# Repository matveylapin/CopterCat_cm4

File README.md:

# CopterCat_cm4

Полётный контроллер для стандарта FMU-v6u. Обычно на дронах для программирования устанавливают полётный контроллер, одноплатный компьютер и иногда arduino. Почему бы не объединить это в одну плату (ну или компактный стек), это уменьшит габариты и вес. В качестве arduino мы выбрали чип ESP32, это позволит организовывать из нескольких подобных плат одну независимую сеть для коммуникации между дронами.

## Спецификация 

### FMU
* STM32H753IIK6 480Mhz Cortex-M7
* 2Mb + 256Kb FLASH
* 1Mb RAM
* ICM20602, ICM42605, BMI088, BMP388, BMM150
* Полностью совместима со стандартом FMU-v6u
### Raspberry Pi
* Поддержка платы RPi CM4 
* Слот для SD-карты
* Возможность прошивки встроенной eMMC
* CAT24C256 EEPROM
* Поддержка 2 камер(CAM0-две линия, CAM1-четыре линии)
* Поддержка USB-OTG
### ESP32
* 16MB внешней FLASH (W25Q128JVS)
* 8MB внешней PSRAM (LY68L6400SLIT)
* Встроенная антенна
* USB-TTL конвертор
### Остальное
* USB-HUB USB2514B
* USB-PD с физическим переключением
* Связь ESP32 и STM32 через UART
* 3 варианта питания
* 4 универсальных GPIO от ESP32
* USB Type-C
* Размеры 40x55 мм, плата 4 слоя
___

## Разьёмы и перемычки

1. GPIO ESP32 4 порта ввода вывода для подключения внешнего оборудования
2. Коннекторы RPi CM4
3. Выводы ESC 8 шт
4. Контакты программирования и отладки JTAG STM32
5. Коннекторы камер (шлейф 22 контакта с 0.5 мм расстояния между проводниками)
6. Контакт подключения адресной ленты
7. Контакты основного питания 5В
8. JST-6 стандартного шлейфа питания PX4 
9. JST-6 GPS+компас+5В
10. JST-4 I2C+5В
11. USB Type-C
12. JST-4 UART7+5В
13. JST-4 I2C RPi+3.3B для подключения дальномера
14. JST-4 UART5+5В
15. JST-5 Стандартный разъём для подключения приёмника управления
16. Слот SD карты (для RPi)
17. Джампер BOOT для STM32
18. Джампер RPIBOOT для прошивки eMMC модуля RPi CM4
19. Джампер переключения режима работы USB разъёма (при замкнутой перемычке, USB работает как вход HUB и при подключении к компьютеру будут отборажаться STM32, ESP32 и RPi CM4 в режиме OTG; при разомкнутой перемычке, USB будет работать для подключения внешних устройств к RPi, например стерео-камеры)
___

## Загрузка прошивки
### FMU
При первом запуске, в микроконтреллер придётся загрузить PX4-bootloader через порт JTAG. Подробная инструкция [здесь](https://docs.px4.io/master/en/software_update/stm32_bootloader.html#stm32-bootloader).

Для подключения к компьютеру:
1. Замкните перемычку 19
2. Подключите USB Type-C к компьютеру
3. Устройство должно появиться в [QGC](http://qgroundcontrol.com)

Также прошивку можно произвести через RPi:
1. Установите RPi CM4 в коннектор на плате
2. Разомкните перемычку 19
3. Устройство появиться в папке /dev на RPi

### ESP32
Написать программу можно либо в [Arduino IDE](https://www.arduino.cc/en/software), либо в [VS Code](https://code.visualstudio.com) с плагином [esp-idf](https://habr.com/ru/post/530638/). Далее скомпилировать и загрузить в микроконтроллер. Загрузить можно двумя способами.

С компьютера:
1. Замкните перемычку 19
2. В подключённых устройствах появиться CP2104
3. Загрузите прошивку в соотвествии с инструкцией к выбранной IDE

С RPi CM4:
1. Установите RPi CM4 в коннектор на плате
2. Разомкните перемычку 19
3. Скомпилируйте ваш код в .bin формат
4. Загрузите полученный файл на RPi
5. Загрузите прошивку в микроконтроллер с помощью esptool.py ([описание+установка](https://docs.espressif.com/projects/esptool/en/latest/esp32/index.html))

Так же ESP32 подключен к STM32 по UART, это позволит связывть между собой не просто RPi, а сразу FMU.

### RPi CM4
Слот SD карты работает как на стандартной RPi. Для плат с eMMC порядок загрузки операционной системы не отличается от CM4 IO Board ([инструкция](https://www.jeffgeerling.com/blog/2020/how-flash-raspberry-pi-os-compute-module-4-emmc-usbboot)).

___

## Общая информация
* Все требуемые для заказа файлы находится в папке /gerbers.
* Проект выполнен в программе [KiCAD v6](https://www.kicad.org)
* Библиотеки компонентов взяты с сайта [snapeda](https://www.snapeda.com)

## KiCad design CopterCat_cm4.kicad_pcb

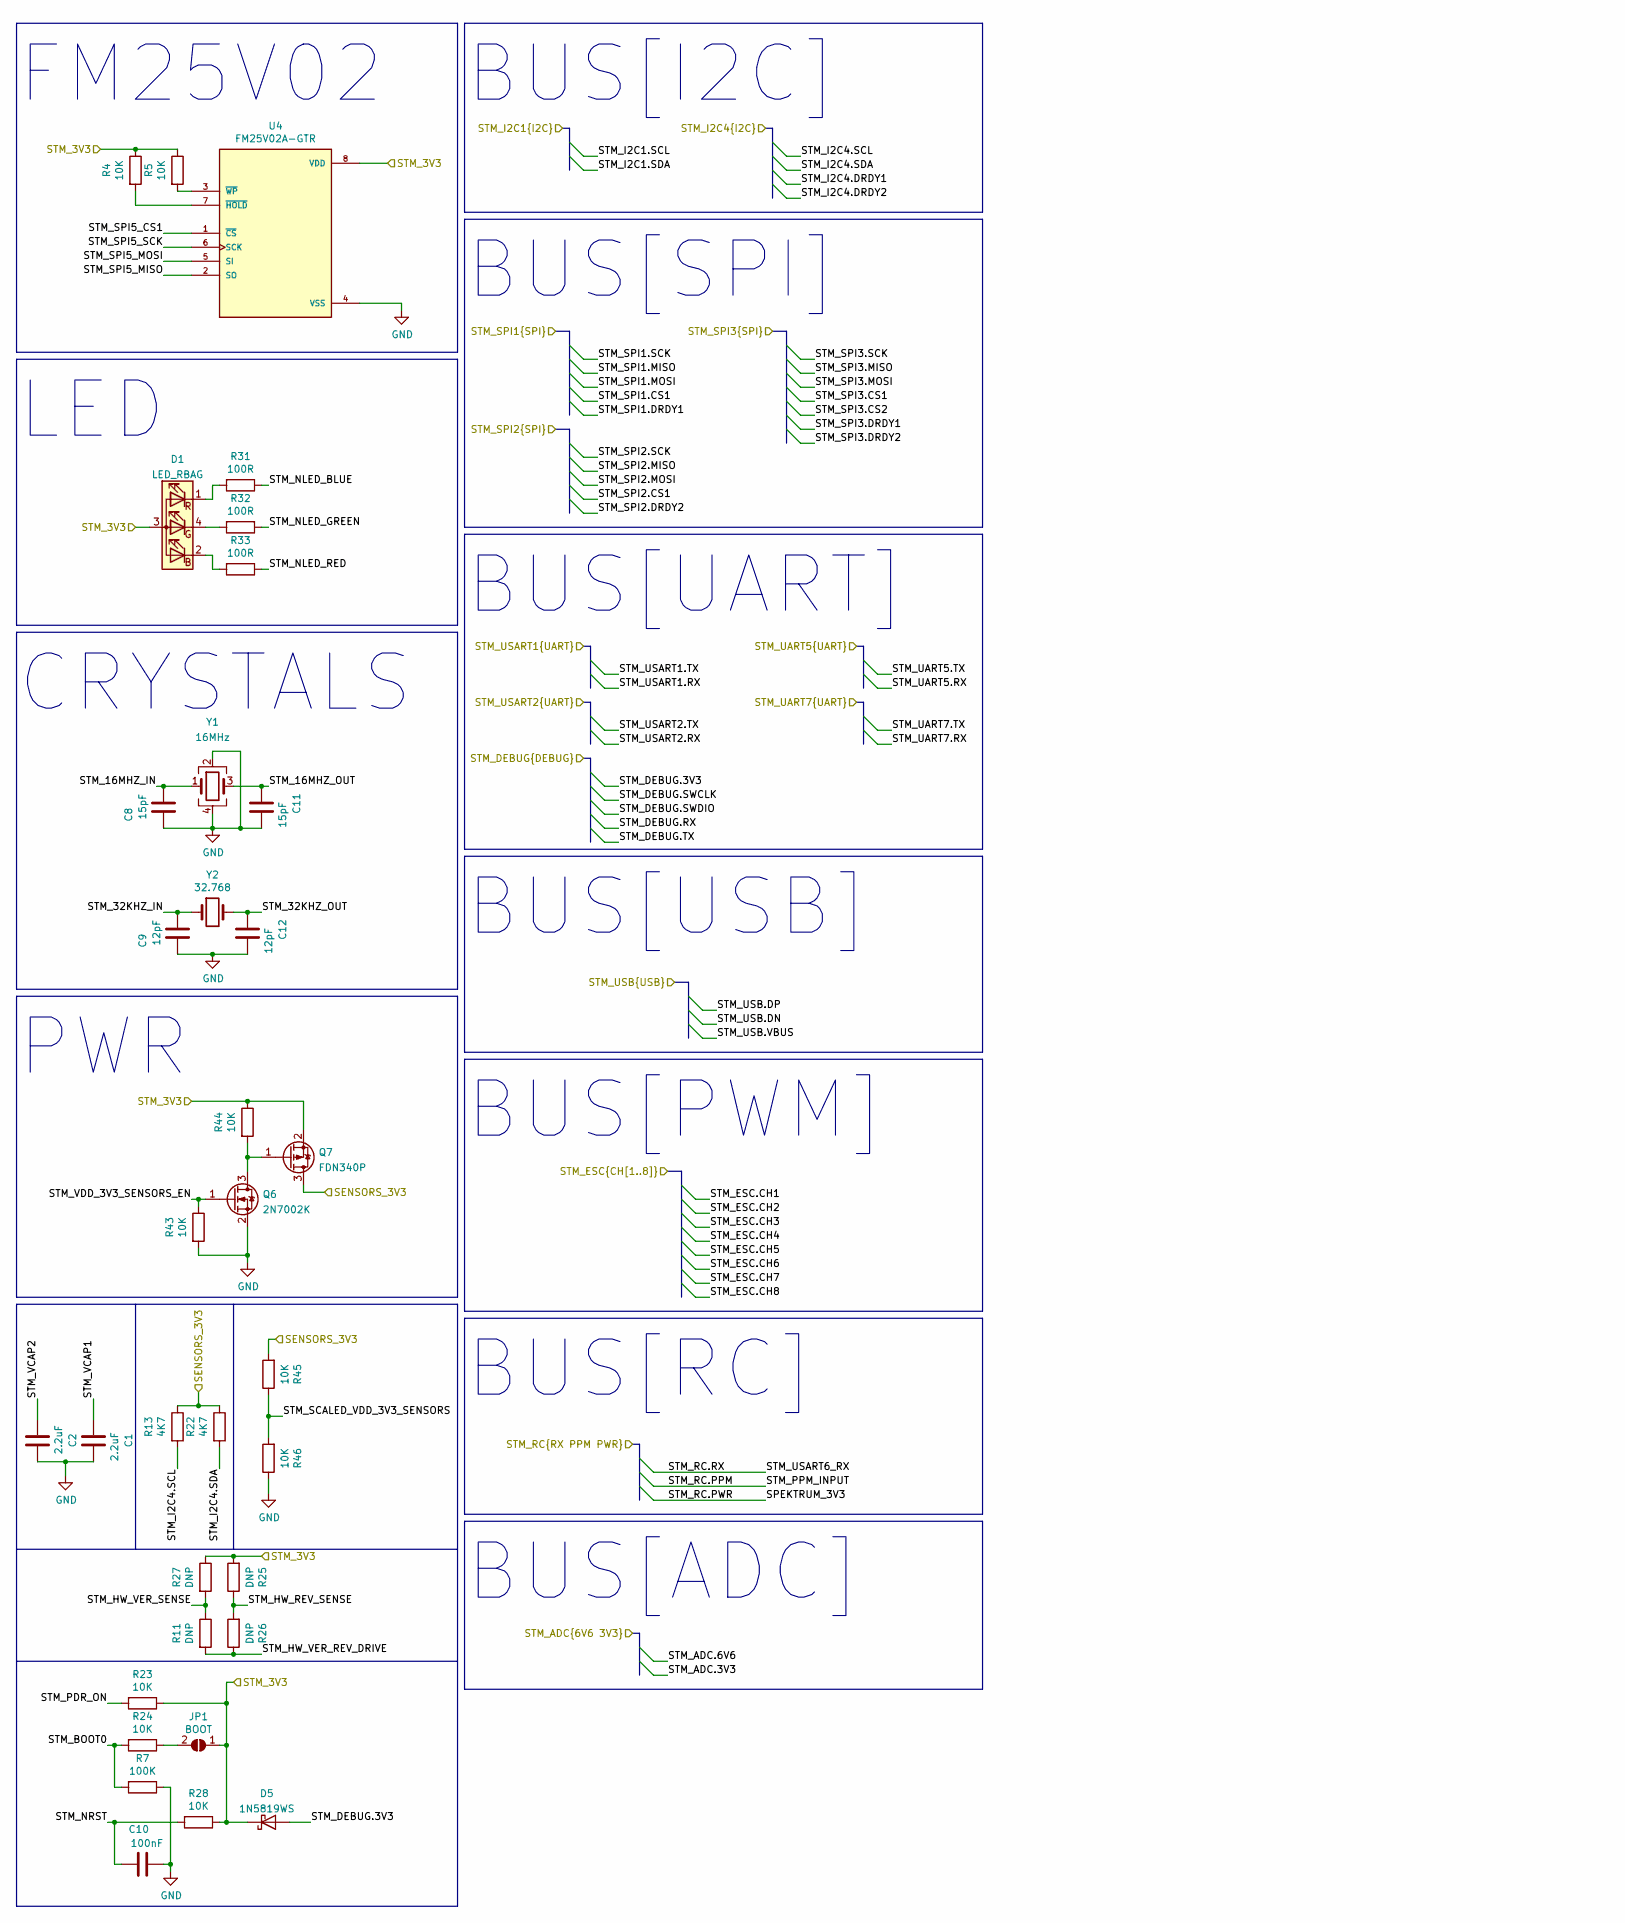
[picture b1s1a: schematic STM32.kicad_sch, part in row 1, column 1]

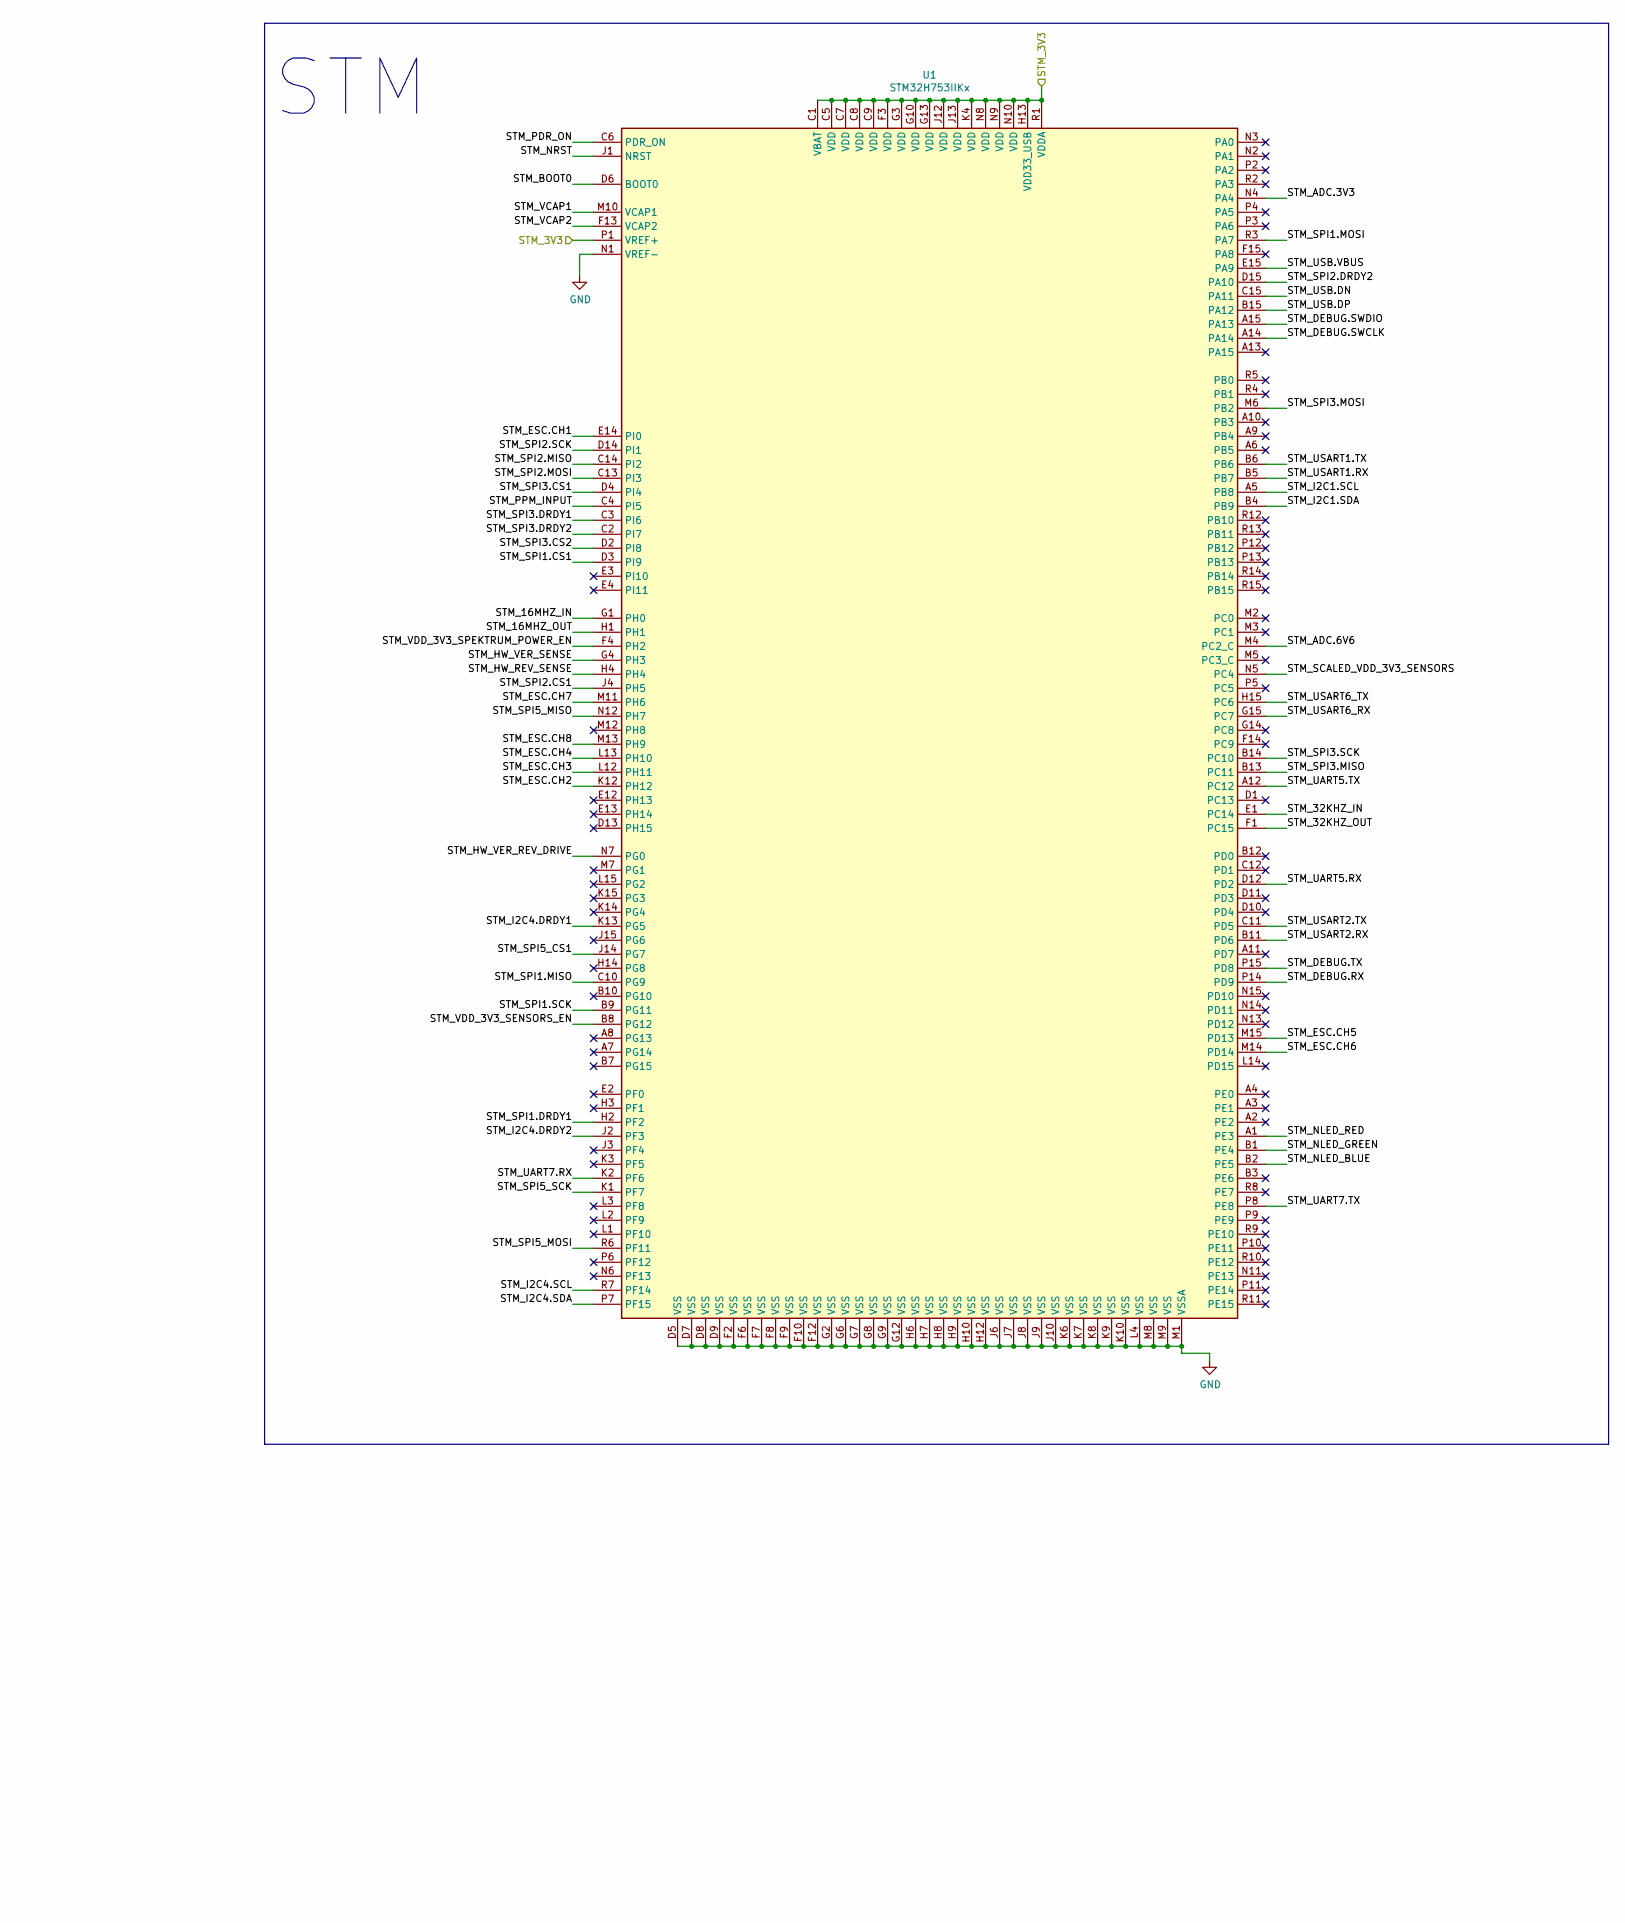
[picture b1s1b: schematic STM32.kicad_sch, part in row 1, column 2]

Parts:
C1, C2: 2.2uF; C_0402_1005Metric
C8, C11: 15pF; C_0402_1005Metric
C9, C12: 12pF; C_0402_1005Metric
C10: 100nF; C_0402_1005Metric
D1: LED_RBAG; LED_Cree-PLCC4_2x2mm_CW; Manufacturer_Part_Number FM-B2020RGBA-HG
D5: 1N5819WS; D_SOD-323; Manufacturer_Part_Number 1N5819WS
JP1: BOOT; SolderJumper-2_P1.3mm_Open_RoundedPad1.0x1.5mm
Q6: 2N7002K; SOT-23; Manufacturer_Part_Number 2N7002,215
Q7: FDN340P; SOT-23; Manufacturer_Part_Number FDN340P
R4, R5, R23, R24, R28, R43, R44, R45, R46: 10K; R_0402_1005Metric
R7: 100K; R_0402_1005Metric
R11, R25, R26, R27: DNP; R_0402_1005Metric
R13, R22: 4K7; R_0402_1005Metric
R31, R32, R33: 100R; R_0402_1005Metric
U1: STM32H753IIKx; UFBGA-201_10x10mm_Layout15x15_P0.65mm; Manufacturer_Part_Number STM32H753IIK6
U4: FM25V02A-GTR; SOIC127P602X172-8N; Manufacturer_Part_Number FM25V02A-GTR
Y1: 16MHz; Crystal_SMD_2016-4Pin_2.0x1.6mm; Manufacturer_Part_Number OT201616MJBA4SL
Y2: 32.768; Crystal_SMD_MicroCrystal_CM9V-T1A-2Pin_1.6x1.0mm; Manufacturer_Part_Number SC-16S

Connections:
/Connectors/STM_ADC.3V3: U1.N4 (PA4); also elsewhere on the board
/Connectors/STM_ADC.6V6: U1.M4 (PC2_C); also elsewhere on the board
/Connectors/STM_DEBUG.3V3: D5.2 (A); also elsewhere on the board
/Connectors/STM_DEBUG.RX: U1.P14 (PD9); also elsewhere on the board
/Connectors/STM_DEBUG.SWCLK: U1.A14; also elsewhere on the board
/Connectors/STM_DEBUG.SWDIO: U1.A15 (PA13); also elsewhere on the board
/Connectors/STM_DEBUG.TX: U1.P15 (PD8); also elsewhere on the board
/Connectors/STM_ESC.CH1: U1.E14 (PI0); also elsewhere on the board
/Connectors/STM_ESC.CH2: U1.K12 (PH12); also elsewhere on the board
/Connectors/STM_ESC.CH3: U1.L12 (PH11); also elsewhere on the board
/Connectors/STM_ESC.CH4: U1.L13 (PH10); also elsewhere on the board
/Connectors/STM_ESC.CH5: U1.M15 (PD13); also elsewhere on the board
/Connectors/STM_ESC.CH6: U1.M14 (PD14); also elsewhere on the board
/Connectors/STM_ESC.CH7: U1.M11 (PH6); also elsewhere on the board
/Connectors/STM_ESC.CH8: U1.M13 (PH9); also elsewhere on the board
/Connectors/STM_I2C1.SCL: U1.A5 (PB8); also elsewhere on the board
/Connectors/STM_I2C1.SDA: U1.B4 (PB9); also elsewhere on the board
/Connectors/STM_RC.PPM: U1.C4 (PI5); also elsewhere on the board
/Connectors/STM_RC.RX: U1.G15 (PC7); also elsewhere on the board
/Connectors/STM_UART5.RX: U1.D12 (PD2); also elsewhere on the board
/Connectors/STM_UART5.TX: U1.A12 (PC12); also elsewhere on the board
/Connectors/STM_UART7.RX: U1.K2 (PF6); also elsewhere on the board
/Connectors/STM_UART7.TX: U1.P8 (PE8); also elsewhere on the board
/Connectors/STM_USART1.RX: U1.B5 (PB7); also elsewhere on the board
/Connectors/STM_USART1.TX: U1.B6; also elsewhere on the board
/ESP32/ESP_UART1.RX: U1.B11 (PD6); also elsewhere on the board
/ESP32/ESP_UART1.TX: U1.C11 (PD5); also elsewhere on the board
/Power/3V3_GROUP1: D1.3 (A), D5.1 (K), JP1.1 (A), Q7.2 (S), R4.1, R5.1, R23.1, R25.2, R27.1, R28.1, R44.1, U1.C1 (VBAT), U1.C5 (VDD), U1.C7 (VDD), U1.C8 (VDD), U1.C9 (VDD), U1.F3 (VDD), U1.G3 (VDD), U1.G10 (VDD), U1.G13 (VDD), U1.H13 (VDD33_USB), U1.J12 (VDD), U1.J13 (VDD), U1.K4 (VDD), U1.N8 (VDD), U1.N9 (VDD), U1.N10 (VDD), U1.P1 (VREF+), U1.R1 (VDDA), U4.8 (VDD); also elsewhere on the board
/STM32/SENSORS_3V3: Q7.3 (D), R13.1, R22.1, R45.2; also elsewhere on the board
/STM32/STM_16MHZ_IN: C8.2, U1.G1 (PH0), Y1.1
/STM32/STM_16MHZ_OUT: C11.1, U1.H1, Y1.3
/STM32/STM_32KHZ_IN: C9.2, U1.E1 (PC14), Y2.1
/STM32/STM_32KHZ_OUT: C12.1, U1.F1 (PC15), Y2.2
/STM32/STM_BOOT0: R7.2, R24.2, U1.D6 (BOOT0)
/STM32/STM_HW_REV_SENSE: R25.1, R26.2, U1.H4
/STM32/STM_HW_VER_REV_DRIVE: R11.2, R26.1, U1.N7 (PG0)
/STM32/STM_HW_VER_SENSE: R11.1, R27.2, U1.G4 (PH3)
/STM32/STM_I2C4.DRDY1: U1.K13 (PG5); also elsewhere on the board
/STM32/STM_I2C4.DRDY2: U1.J2 (PF3); also elsewhere on the board
/STM32/STM_I2C4.SCL: R13.2, U1.R7 (PF14); also elsewhere on the board
/STM32/STM_I2C4.SDA: R22.2, U1.P7 (PF15); also elsewhere on the board
/STM32/STM_NLED_BLUE: R31.1, U1.B2 (PE5)
/STM32/STM_NLED_GREEN: R32.2, U1.B1 (PE4)
/STM32/STM_NLED_RED: R33.1, U1.A1 (PE3)
/STM32/STM_NRST: C10.1, R28.2, U1.J1 (NRST)
/STM32/STM_PDR_ON: R23.2, U1.C6 (PDR_ON)
/STM32/STM_SCALED_VDD_3V3_SENSORS: R45.1, R46.2, U1.N5 (PC4)
/STM32/STM_SPI1.CS1: U1.D3 (PI9); also elsewhere on the board
/STM32/STM_SPI1.DRDY1: U1.H2 (PF2); also elsewhere on the board
/STM32/STM_SPI1.MISO: U1.C10 (PG9); also elsewhere on the board
/STM32/STM_SPI1.MOSI: U1.R3 (PA7); also elsewhere on the board
/STM32/STM_SPI1.SCK: U1.B9 (PG11); also elsewhere on the board
/STM32/STM_SPI2.CS1: U1.J4 (PH5); also elsewhere on the board
/STM32/STM_SPI2.DRDY2: U1.D15 (PA10); also elsewhere on the board
/STM32/STM_SPI2.MISO: U1.C14 (PI2); also elsewhere on the board
/STM32/STM_SPI2.MOSI: U1.C13 (PI3); also elsewhere on the board
/STM32/STM_SPI2.SCK: U1.D14 (PI1); also elsewhere on the board
/STM32/STM_SPI3.CS1: U1.D4 (PI4); also elsewhere on the board
/STM32/STM_SPI3.CS2: U1.D2 (PI8); also elsewhere on the board
/STM32/STM_SPI3.DRDY1: U1.C3 (PI6); also elsewhere on the board
/STM32/STM_SPI3.DRDY2: U1.C2 (PI7); also elsewhere on the board
/STM32/STM_SPI3.MISO: U1.B13 (PC11); also elsewhere on the board
/STM32/STM_SPI3.MOSI: U1.M6 (PB2); also elsewhere on the board
/STM32/STM_SPI3.SCK: U1.B14 (PC10); also elsewhere on the board
/STM32/STM_SPI5_CS1: U1.J14 (PG7), U4.1 (~CS)
/STM32/STM_SPI5_MISO: U1.N12 (PH7), U4.2 (SO)
/STM32/STM_SPI5_MOSI: U1.R6 (PF11), U4.5 (SI)
/STM32/STM_SPI5_SCK: U1.K1 (PF7), U4.6 (SCK)
/STM32/STM_USART6_TX: U1.H15 (PC6)
/STM32/STM_USB.DN: U1.C15 (PA11); also elsewhere on the board
/STM32/STM_USB.DP: U1.B15 (PA12); also elsewhere on the board
/STM32/STM_USB.VBUS: U1.E15 (PA9); also elsewhere on the board
/STM32/STM_VCAP1: C1.1, U1.M10 (VCAP1)
/STM32/STM_VCAP2: C2.1, U1.F13 (VCAP2)
/STM32/STM_VDD_3V3_SENSORS_EN: Q6.1 (G), R43.1, U1.B8 (PG12)
/STM32/STM_VDD_3V3_SPEKTRUM_POWER_EN: U1.F4 (PH2)
GND: C1.2, C2.2, C8.1, C9.1, C10.2, C11.2, C12.2, Q6.2 (S), R7.1, R43.2, R46.1, U1.D5 (VSS), U1.D7 (VSS), U1.D8 (VSS), U1.D9 (VSS), U1.F2 (VSS), U1.F6 (VSS), U1.F7 (VSS), U1.F8 (VSS), U1.F9 (VSS), U1.F10 (VSS), U1.F12 (VSS), U1.G2 (VSS), U1.G6 (VSS), U1.G7 (VSS), U1.G8 (VSS), U1.G9 (VSS), U1.G12 (VSS), U1.H6 (VSS), U1.H7 (VSS), U1.H8 (VSS), U1.H9 (VSS), U1.H10 (VSS), U1.H12 (VSS), U1.J6 (VSS), U1.J7 (VSS), U1.J8 (VSS), U1.J9 (VSS), U1.J10 (VSS), U1.K6 (VSS), U1.K7 (VSS), U1.K8 (VSS), U1.K9 (VSS), U1.K10 (VSS), U1.L4 (VSS), U1.M1 (VSSA), U1.M8 (VSS), U1.M9 (VSS), U1.N1 (VREF-), U4.4 (VSS), Y1.2, Y1.4; also elsewhere on the board
unnamed: D1.1 (RK), R31.2
unnamed: D1.2 (BK), R33.2
unnamed: D1.4 (GK), R32.1
unnamed: JP1.2 (B), R24.1
unnamed: Q6.3 (D), Q7.1 (G), R44.2
unnamed: R4.2, U4.7 (~HOLD)
unnamed: R5.2, U4.3 (~WP)

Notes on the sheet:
BUS[RC]
BUS[SPI]
PWR
BUS[UART]
CRYSTALS
FM25V02
BUS[USB]
STM
BUS[ADC]
LED
BUS[PWM]
BUS[I2C]

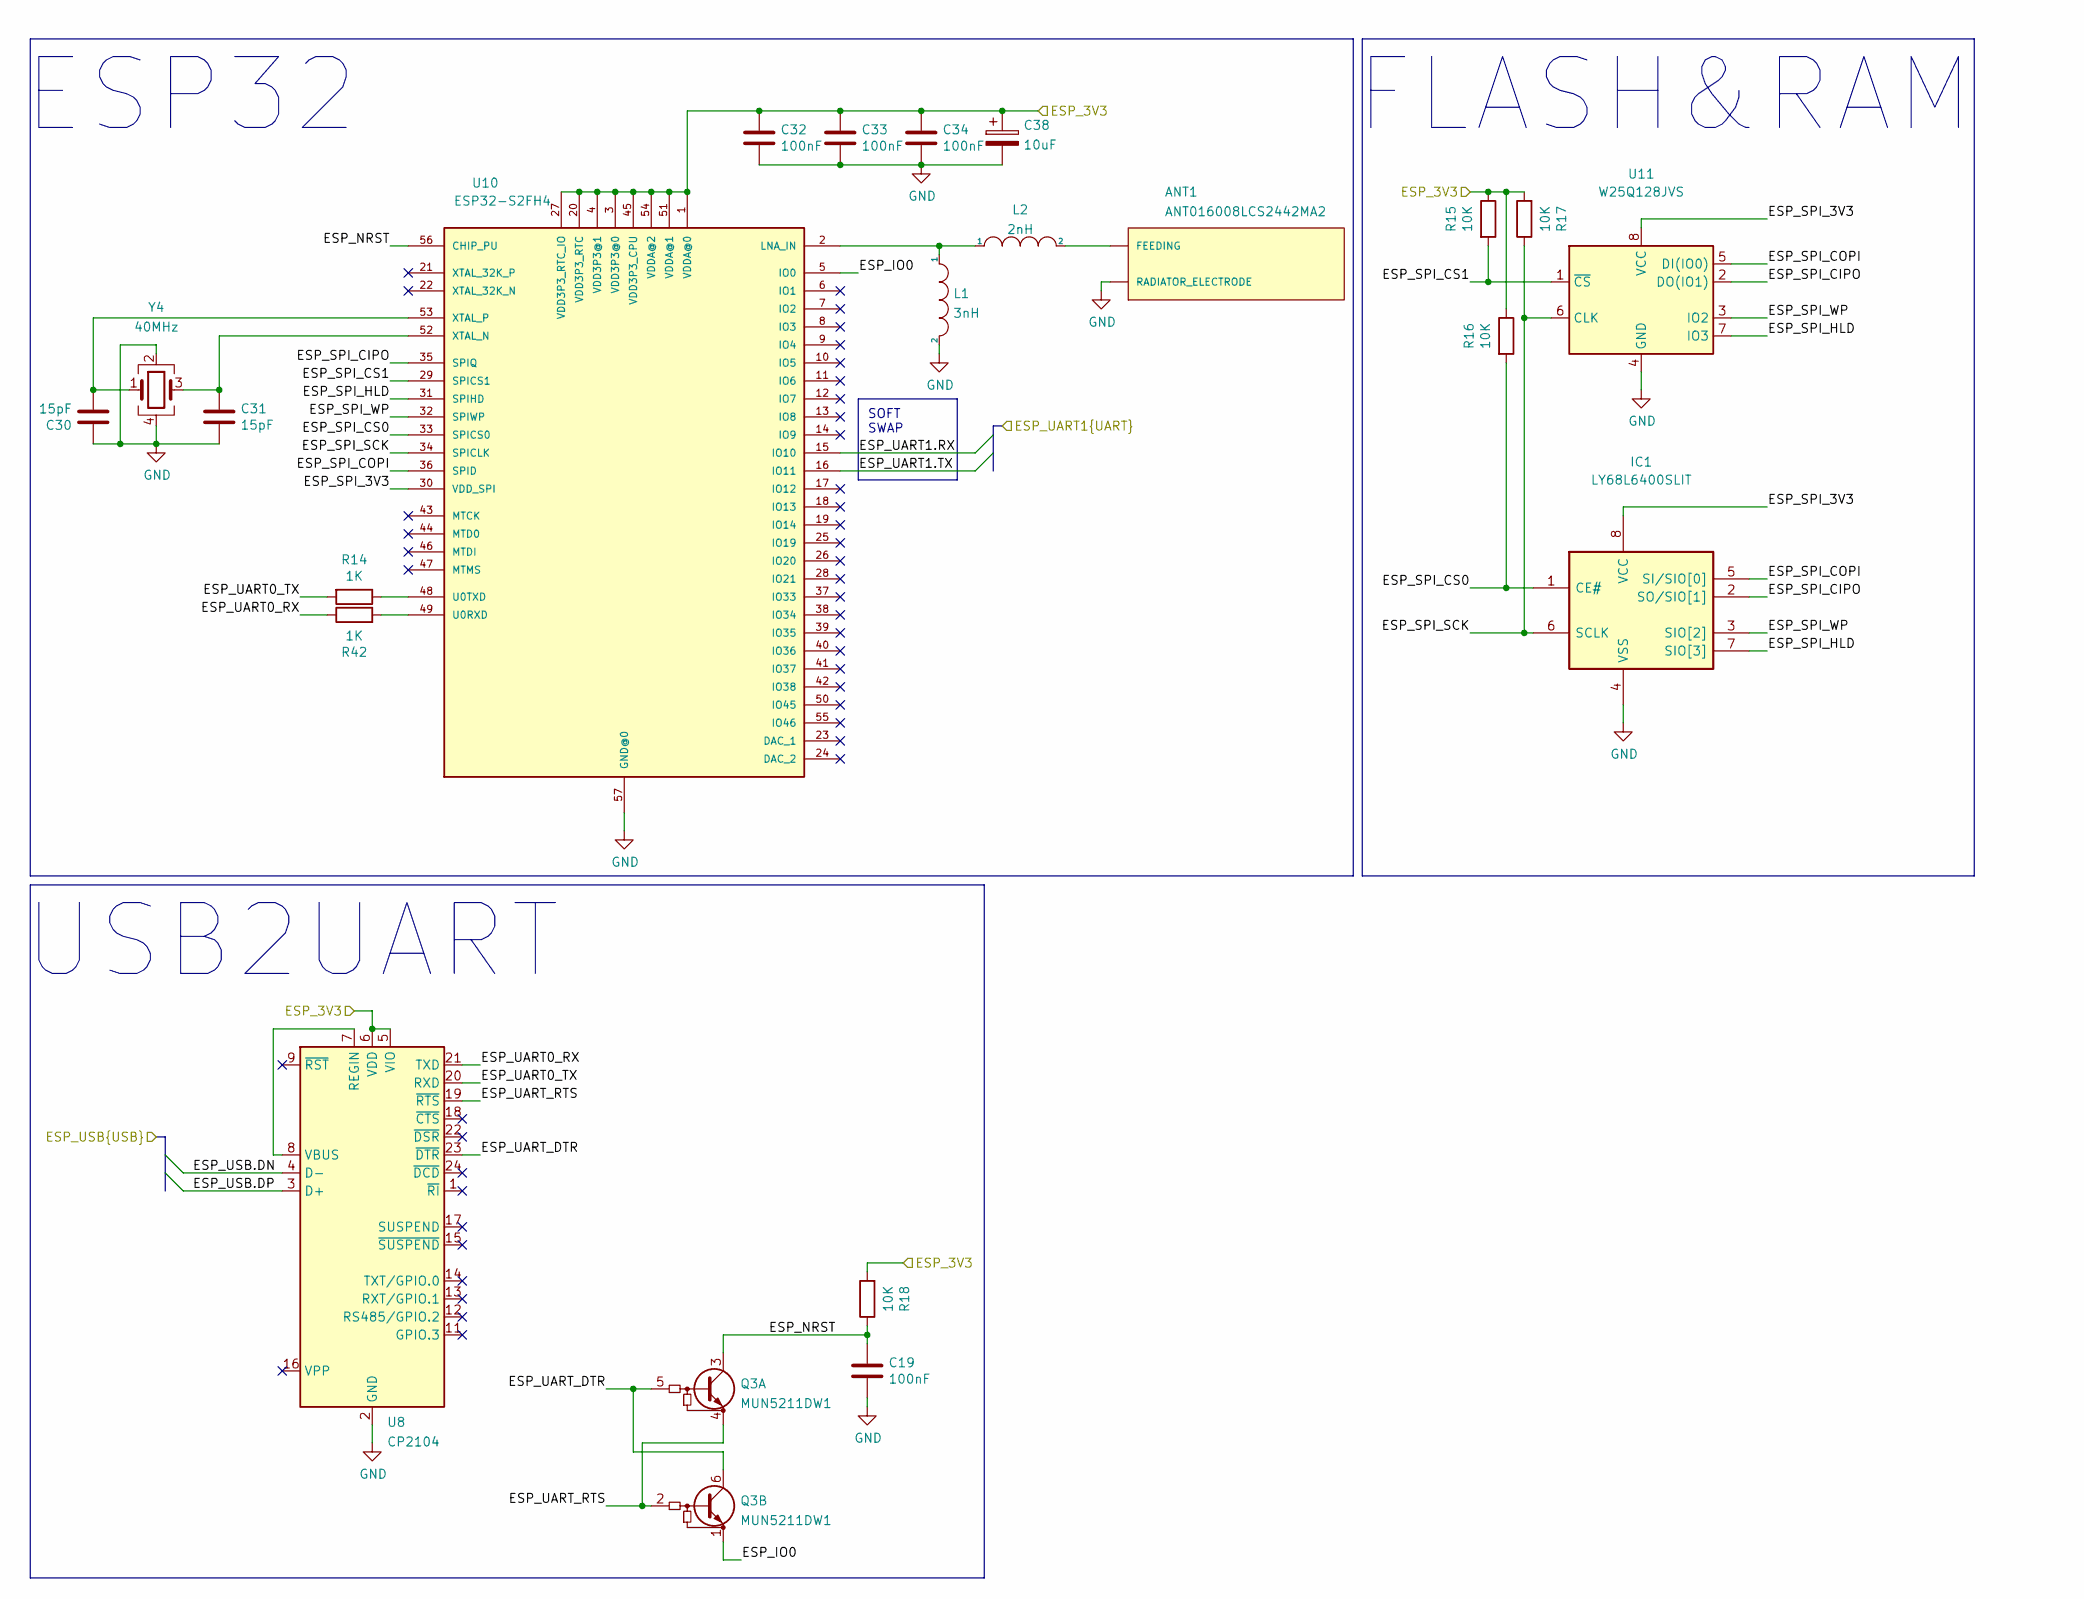
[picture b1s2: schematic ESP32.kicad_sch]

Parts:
ANT1: ANT016008LCS2442MA2; ANT_ANT016008LCS2442MA2; Manufacturer_Part_Number ANT016008LCS2442MA2
C19, C32, C33, C34: 100nF; C_0402_1005Metric
C30, C31: 15pF; C_0402_1005Metric
C38: 10uF; CP_EIA-3216-18_Kemet-A; Manufacturer_Part_Number CL31A226KAHNNNE
IC1: LY68L6400SLIT; SOIC127P600X175-8N; Manufacturer_Part_Number LY68L6400SLIT
L1: 3nH; L_0402_1005Metric; Manufacturer_Part_Number SDCL1005C2N0STDF
L2: 2nH; L_0402_1005Metric; Manufacturer_Part_Number SDCL1005C2N0STDF
Q3: MUN5211DW1; SOT-363_SC-70-6; Manufacturer_Part_Number MUN5211DW1T1G
R14, R42: 1K; R_0402_1005Metric
R15, R16, R17, R18: 10K; R_0402_1005Metric
U8: CP2104; QFN-24-1EP_4x4mm_P0.5mm_EP2.6x2.6mm; Manufacturer_Part_Number CP2104-F03-GMR
U10: ESP32-S2FH4; QFN40P700X700X90-57T400N; Manufacturer_Part_Number ESP32-S2FH4
U11: W25Q128JVS; SOIC-8_5.23x5.23mm_P1.27mm; Manufacturer_Part_Number W25Q128JVS
Y4: 40MHz; Crystal_SMD_2016-4Pin_2.0x1.6mm; Manufacturer_Part_Number OT201640MJBA4SL

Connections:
/ESP32/ESP_3V3: C32.1, C33.1, C34.1, C38.1, R15.1, R16.1, R17.2, R18.2, U8.5 (VIO), U8.6 (VDD), U10.1 (VDDA@0), U10.3 (VDD3P3@0), U10.4 (VDD3P3@1), U10.20 (VDD3P3_RTC), U10.27 (VDD3P3_RTC_IO), U10.45 (VDD3P3_CPU), U10.51 (VDDA@1), U10.54 (VDDA@2); also elsewhere on the board
/ESP32/ESP_IO0: Q3.1 (E2), U10.5 (IO0)
/ESP32/ESP_NRST: C19.1, Q3.3 (C1), R18.1, U10.56 (CHIP_PU)
/ESP32/ESP_SPI_3V3: IC1.8 (VCC), U10.30 (VDD_SPI), U11.8 (VCC)
/ESP32/ESP_SPI_CIPO: IC1.2 (SO/SIO[1]), U10.35 (SPIQ), U11.2 (DO(IO1))
/ESP32/ESP_SPI_COPI: IC1.5 (SI/SIO[0]), U10.36 (SPID), U11.5 (DI(IO0))
/ESP32/ESP_SPI_CS0: IC1.1 (CE#), R16.2, U10.33 (SPICS0)
/ESP32/ESP_SPI_CS1: R15.2, U10.29 (SPICS1), U11.1 (~CS)
/ESP32/ESP_SPI_HLD: IC1.7 (SIO[3]), U10.31 (SPIHD), U11.7 (IO3)
/ESP32/ESP_SPI_SCK: IC1.6 (SCLK), R17.1, U10.34 (SPICLK), U11.6 (CLK)
/ESP32/ESP_SPI_WP: IC1.3 (SIO[2]), U10.32 (SPIWP), U11.3 (IO2)
/ESP32/ESP_UART0_RX: R42.1, U8.21 (TXD)
/ESP32/ESP_UART0_TX: R14.2, U8.20 (RXD)
/ESP32/ESP_UART1.RX: U10.15 (IO10); also elsewhere on the board
/ESP32/ESP_UART1.TX: U10.16 (IO11); also elsewhere on the board
/ESP32/ESP_UART_DTR: Q3.5 (B1), Q3.6 (C2), U8.23 (~DTR)
/ESP32/ESP_UART_RTS: Q3.2 (B2), Q3.4 (E1), U8.19 (~RTS)
/ESP32/ESP_USB.DN: U8.4 (D-); also elsewhere on the board
/ESP32/ESP_USB.DP: U8.3 (D+); also elsewhere on the board
GND: ANT1.1 (RADIATOR_ELECTRODE), C19.2, C30.1, C31.2, C32.2, C33.2, C34.2, C38.2, IC1.4 (VSS), L1.2, U8.2 (GND), U8.25 (GND), U10.57 (GND@0), U11.4 (GND), Y4.2, Y4.4; also elsewhere on the board
unnamed: ANT1.4 (FEEDING), L2.2
unnamed: C30.2, U10.53 (XTAL_P), Y4.1
unnamed: C31.1, U10.52 (XTAL_N), Y4.3
unnamed: L1.1, L2.1, U10.2 (LNA_IN)
unnamed: R14.1, U10.48 (U0TXD)
unnamed: R42.2, U10.49 (U0RXD)
unnamed: U8.7 (REGIN), U8.8 (VBUS)

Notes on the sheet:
ESP32
FLASH&RAM
USB2UART
SOFT SWAP

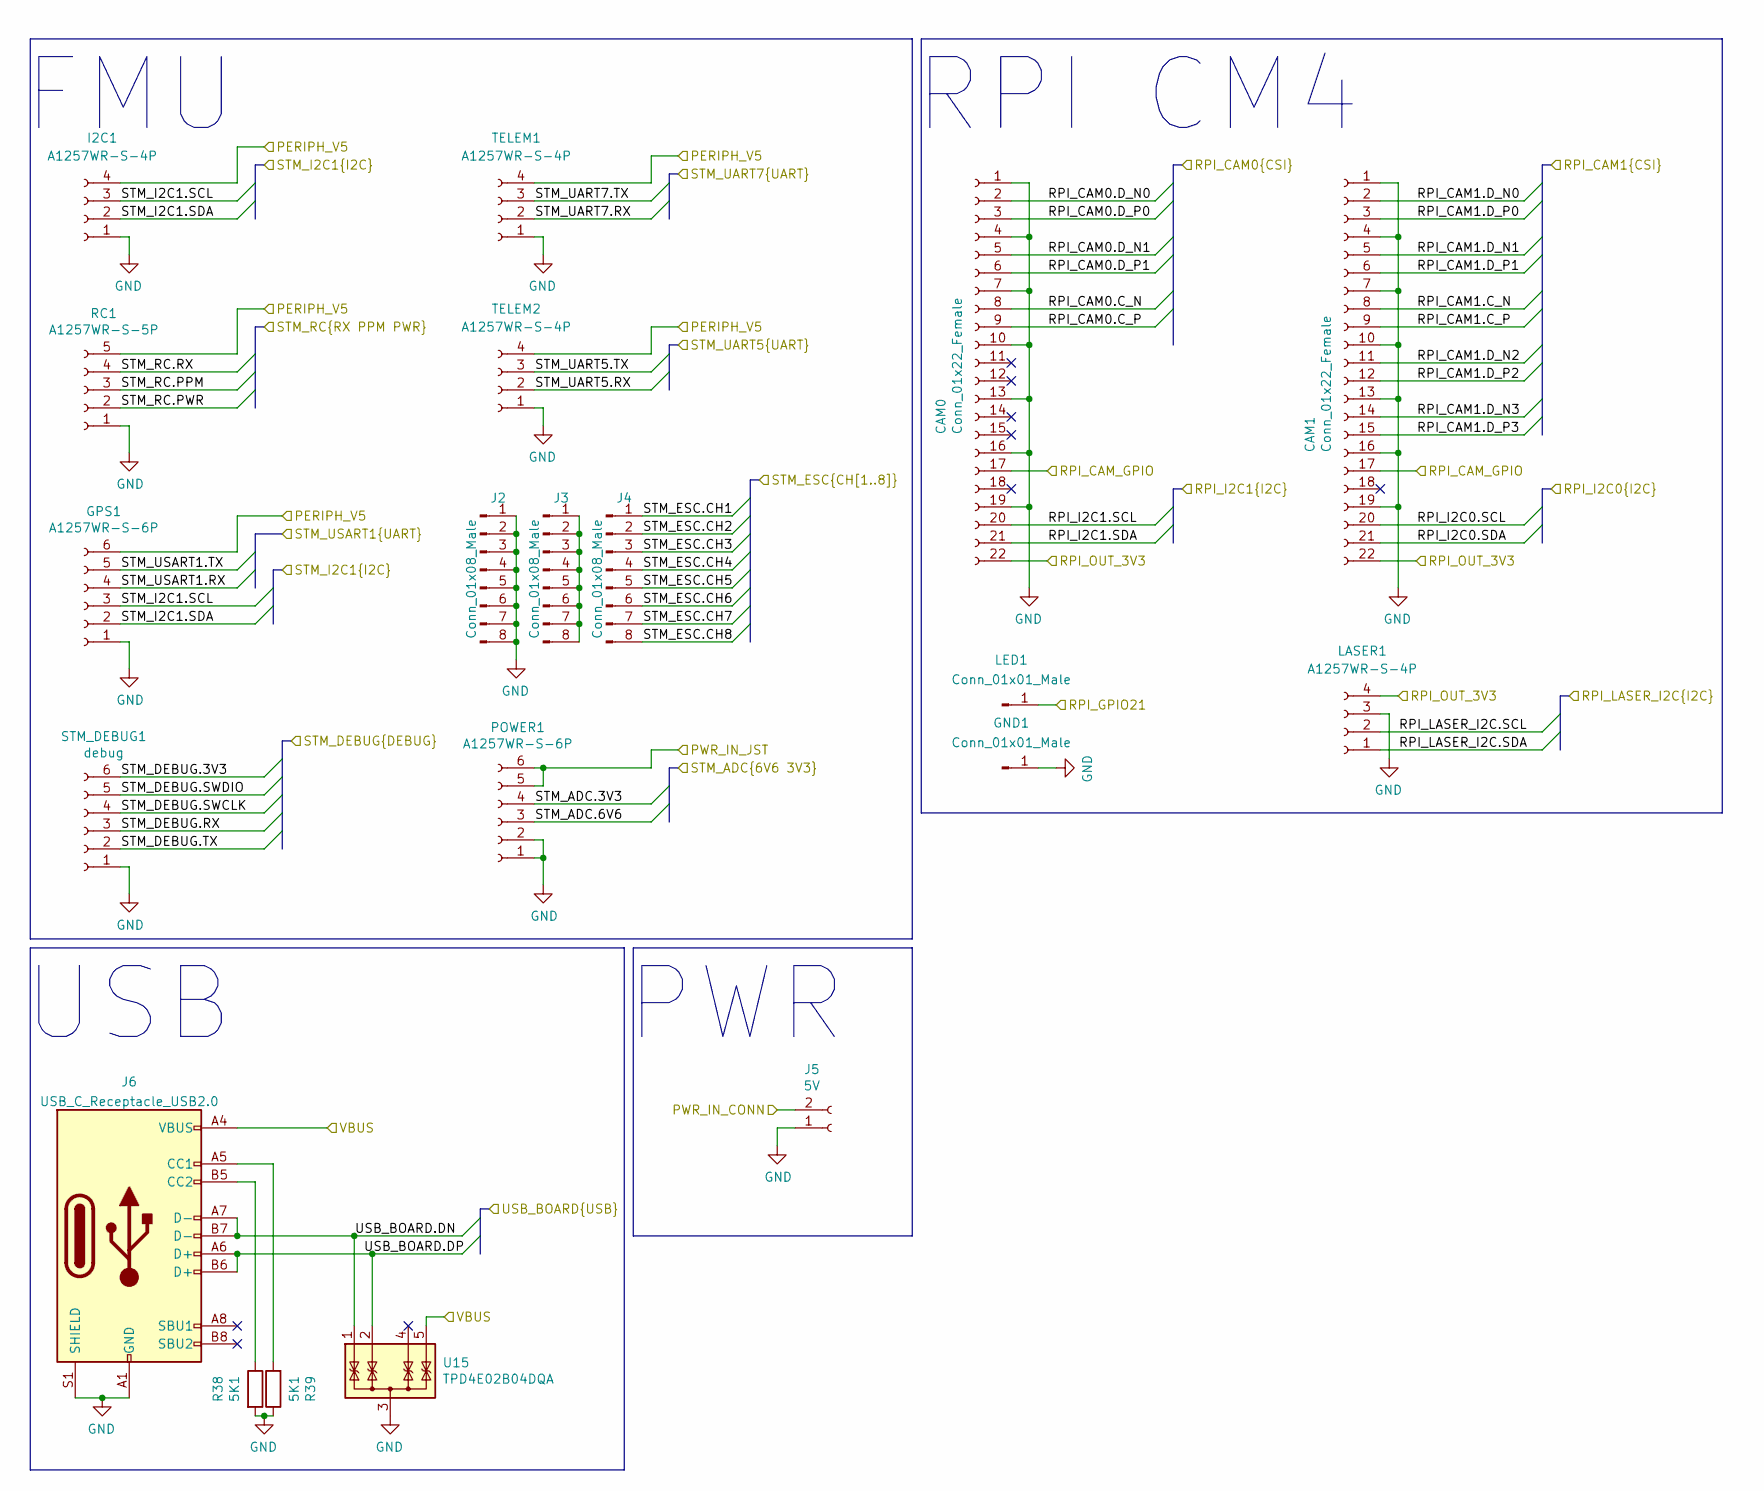
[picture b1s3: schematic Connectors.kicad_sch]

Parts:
CAM0, CAM1: Conn_01x22_Female; Hirose_FH12-22S-0.5SH_1x22-1MP_P0.50mm_Horizontal; Manufacturer_Part_Number AFC04-S22ECA-00
GND1: Conn_01x01_Male; TestPoint_Pad_D1.5mm
GPS1: A1257WR-S-6P; JST_GH_SM06B-GHS-TB_1x06-1MP_P1.25mm_Horizontal; Manufacturer_Part_Number A1257WR-S-6P
I2C1: A1257WR-S-4P; JST_GH_SM04B-GHS-TB_1x04-1MP_P1.25mm_Horizontal; Manufacturer_Part_Number A1257WR-S-4P
J2, J3, J4: Conn_01x08_Male; PinHeader_1x08_P2.54mm_Vertical
J5: 5V; power_pad; Manufacturer_Part_Number XT30U-M
J6: USB_C_Receptacle_USB2.0; USB_C_Receptacle_HRO_TYPE-C-31-M-12; Manufacturer_Part_Number 918-418K2023S40001
LASER1: A1257WR-S-4P; JST_GH_SM04B-GHS-TB_1x04-1MP_P1.25mm_Horizontal; Manufacturer_Part_Number A1257WR-S-4P
LED1: Conn_01x01_Male; TestPoint_Pad_D1.5mm
POWER1: A1257WR-S-6P; JST_GH_SM06B-GHS-TB_1x06-1MP_P1.25mm_Horizontal; Manufacturer_Part_Number A1257WR-S-6P
R38, R39: 5K1; R_0402_1005Metric
RC1: A1257WR-S-5P; JST_GH_SM05B-GHS-TB_1x05-1MP_P1.25mm_Horizontal; Manufacturer_Part_Number A1257WR-S-5P
STM_DEBUG1: debug; debug_port
TELEM1, TELEM2: A1257WR-S-4P; JST_GH_SM04B-GHS-TB_1x04-1MP_P1.25mm_Horizontal; Manufacturer_Part_Number A1257WR-S-4P
U15: TPD4E02B04DQA; USON-10_2.5x1.0mm_P0.5mm; Manufacturer_Part_Number TPD4E02B04DQA

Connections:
/Connectors/PWR_IN_CONN: J5.2; also elsewhere on the board
/Connectors/PWR_IN_JST: POWER1.5, POWER1.6; also elsewhere on the board
/Connectors/RPI_CAM0.C_N: CAM0.8; also elsewhere on the board
/Connectors/RPI_CAM0.C_P: CAM0.9; also elsewhere on the board
/Connectors/RPI_CAM0.D_N0: CAM0.2; also elsewhere on the board
/Connectors/RPI_CAM0.D_N1: CAM0.5; also elsewhere on the board
/Connectors/RPI_CAM0.D_P0: CAM0.3; also elsewhere on the board
/Connectors/RPI_CAM0.D_P1: CAM0.6; also elsewhere on the board
/Connectors/RPI_CAM1.C_N: CAM1.8; also elsewhere on the board
/Connectors/RPI_CAM1.C_P: CAM1.9; also elsewhere on the board
/Connectors/RPI_CAM1.D_N0: CAM1.2; also elsewhere on the board
/Connectors/RPI_CAM1.D_N1: CAM1.5; also elsewhere on the board
/Connectors/RPI_CAM1.D_N2: CAM1.11; also elsewhere on the board
/Connectors/RPI_CAM1.D_N3: CAM1.14; also elsewhere on the board
/Connectors/RPI_CAM1.D_P0: CAM1.3; also elsewhere on the board
/Connectors/RPI_CAM1.D_P1: CAM1.6; also elsewhere on the board
/Connectors/RPI_CAM1.D_P2: CAM1.12; also elsewhere on the board
/Connectors/RPI_CAM1.D_P3: CAM1.15; also elsewhere on the board
/Connectors/RPI_CAM_GPIO: CAM0.17, CAM1.17; also elsewhere on the board
/Connectors/RPI_GPIO21: LED1.1; also elsewhere on the board
/Connectors/RPI_I2C0.SDA: CAM1.21; also elsewhere on the board
/Connectors/RPI_I2C1.SDA: CAM0.21; also elsewhere on the board
/Connectors/RPI_LASER_I2C.SCL: LASER1.2; also elsewhere on the board
/Connectors/RPI_LASER_I2C.SDA: LASER1.1; also elsewhere on the board
/Connectors/RPI_OUT_3V3: CAM0.22, CAM1.22, LASER1.4; also elsewhere on the board
/Connectors/STM_ADC.3V3: POWER1.4; also elsewhere on the board
/Connectors/STM_ADC.6V6: POWER1.3; also elsewhere on the board
/Connectors/STM_DEBUG.3V3: STM_DEBUG1.6; also elsewhere on the board
/Connectors/STM_DEBUG.RX: STM_DEBUG1.3; also elsewhere on the board
/Connectors/STM_DEBUG.SWCLK: STM_DEBUG1.4; also elsewhere on the board
/Connectors/STM_DEBUG.SWDIO: STM_DEBUG1.5; also elsewhere on the board
/Connectors/STM_DEBUG.TX: STM_DEBUG1.2; also elsewhere on the board
/Connectors/STM_ESC.CH1: J4.1; also elsewhere on the board
/Connectors/STM_ESC.CH2: J4.2; also elsewhere on the board
/Connectors/STM_ESC.CH3: J4.3; also elsewhere on the board
/Connectors/STM_ESC.CH4: J4.4; also elsewhere on the board
/Connectors/STM_ESC.CH5: J4.5; also elsewhere on the board
/Connectors/STM_ESC.CH6: J4.6; also elsewhere on the board
/Connectors/STM_ESC.CH7: J4.7; also elsewhere on the board
/Connectors/STM_ESC.CH8: J4.8; also elsewhere on the board
/Connectors/STM_I2C1.SCL: GPS1.3, I2C1.3; also elsewhere on the board
/Connectors/STM_I2C1.SDA: GPS1.2, I2C1.2; also elsewhere on the board
/Connectors/STM_RC.PPM: RC1.3; also elsewhere on the board
/Connectors/STM_RC.PWR: RC1.2
/Connectors/STM_RC.RX: RC1.4; also elsewhere on the board
/Connectors/STM_UART5.RX: TELEM2.2; also elsewhere on the board
/Connectors/STM_UART5.TX: TELEM2.3; also elsewhere on the board
/Connectors/STM_UART7.RX: TELEM1.2; also elsewhere on the board
/Connectors/STM_UART7.TX: TELEM1.3; also elsewhere on the board
/Connectors/STM_USART1.RX: GPS1.4; also elsewhere on the board
/Connectors/STM_USART1.TX: GPS1.5; also elsewhere on the board
/Connectors/USB_BOARD.DN: J6.A7 (D-), J6.B7 (D-), U15.1 (IO1); also elsewhere on the board
/Connectors/USB_BOARD.DP: J6.A6 (D+), J6.B6 (D+), U15.2 (IO2); also elsewhere on the board
/STM32/STM_USB.VBUS: J6.A4 (VBUS), J6.A9 (VBUS), J6.B4 (VBUS), J6.B9 (VBUS), U15.5 (IO4); also elsewhere on the board
GND: CAM0.1, CAM0.4, CAM0.7, CAM0.10, CAM0.13, CAM0.16, CAM0.19, CAM1.1, CAM1.4, CAM1.7, CAM1.10, CAM1.13, CAM1.16, CAM1.19, GND1.1, GPS1.1, I2C1.1, J2.1, J2.2, J2.3, J2.4, J2.5, J2.6, J2.7, J2.8, J5.1, J6.A1 (GND), J6.A12 (GND), J6.B1 (GND), J6.B12 (GND), J6.S1 (SHIELD), LASER1.3, POWER1.1, POWER1.2, R38.2, R39.1, RC1.1, STM_DEBUG1.1, TELEM1.1, TELEM2.1, U15.3 (G), U15.8 (G); also elsewhere on the board
unnamed: J3.1, J3.2, J3.3, J3.4, J3.5, J3.6, J3.7, J3.8
unnamed: J6.A5 (CC1), R39.2
unnamed: J6.B5 (CC2), R38.1
VCC: GPS1.6, I2C1.4, RC1.5, TELEM1.4, TELEM2.4; also elsewhere on the board

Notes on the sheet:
USB
RPI CM4
FMU
PWR
